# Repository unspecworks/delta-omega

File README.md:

# DELTA OMEGA

A portable ultra-low-profile (ULP) wireless 3×5+2 split keyboard.

## Overview

- Switch support: Cherry MX ULP or Kailh PG1316s
- 34 keys, splayed and staggered with choc spacing
- Wireless
- CNC aluminum case

## Parameters

## Documentation

> [!NOTE]
> This is **not** a typical low-profile (LP) or MX build. While it may look familiar, there are enough differences here that skipping the documentation could cause issues. Please take the time to read all notes and guides before starting.

- [Getting Started](./docs/GETTING_STARTED.md)
- [Bill of Materials](./docs/BOM.md)
- [Build Guides](./docs/BUILD_GUIDES.md)
- [Video](https://youtu.be/UktrqN3MlLI)
- [PCB](./pcb/README.md)
- [Case](./case/README.md)
- [ZMK Keyboard Module](https://github.com/unspecworks/zmk-keyboard-delta-omega)
- [Pre-conf ZMK Config](https://github.com/unspecworks/zmk-delta-omega)
- Keycaps
  - [Delta ULP Keycap](https://github.com/unspecworks/delta-ulp-keycap)

## Photos

- [Gallery](./gallery/README.md)
- [Prototype Gallery](./images/README.md)
  - Diff: Port position, Thumb-cluster layout and only hot-plate way.

## Acknowledgments and Inspirations

- [GEIGEIGEIST/TOTEM](https://github.com/GEIGEIGEIST/TOTEM)
- [mikeholscher/zmk-config-mikecinq](https://github.com/mikeholscher/zmk-config-mikecinq)
- [pashutk/Cherry_MX_ULP](https://github.com/pashutk/Cherry_MX_ULP)
- [zmk-rgbled-widget](https://github.com/caksoylar/zmk-rgbled-widget)
- [infused-kim/kb_ergogen_fp](https://github.com/infused-kim/kb_ergogen_fp)
- [ceoloide/ergogen-footprints](https://github.com/ceoloide/ergogen-footprints)
- [kiswitch/kiswitch](https://github.com/kiswitch/kiswitch)

## Limitations and Disclaimer

This is a hobby-driven project. Some aspects may be incomplete, imperfect, or problematic. Use this project **at your own risk**, and note that no warranties or guarantees are provided.

## License

DELTA OMEGA is licensed under [CERN-OHL-W-2.0](./LICENSE.md).

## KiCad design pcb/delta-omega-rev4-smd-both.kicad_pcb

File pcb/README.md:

# PCB

> [!TIP]
> If this is your first visit, please read the [Getting Started guide](./../docs/GETTING_STARTED.md) first.

---

## PCB List

| File | Description | Note |
|---|---|---|
| `delta-omega-rev4-handsolder-both` | Main Left & Right PCB with mouse-bite connection | MB Not tested. |
| `delta-omega-rev4-handsolder-left` | Main Left PCB | |
| `delta-omega-rev4-handsolder-right` | Main Right PCB | |
| `delta_omega_bottom_cover` | Bottom cover PCB plate | Reversible |
| ... |  |  |
| `delta-omega-rev4-smd-both` | SMD Version | :warning: NOT TESTED |

---

## How to Order

This guide is written based on **[JLCPCB](https://jlcpcb.com)**. While other PCB manufacturers may differ slightly, most ordering steps are very similar.

To place an order, you will need the **Gerber archive**. Simply upload the ZIP file found in [./gerbers/](./gerbers/) to the JLCPCB order page.

> [!NOTE]
> In JLCPCB’s Gerber Viewer, the edge cuts for hand-soldering switch may not appear. This is a known JLCPCB viewer issue and does **not** affect the actual manufacturing.

---

### Recommended Options

| Specification     | Recommended                          | Notes                                                                 |
|-------------------|--------------------------------------|----------------------------------------------------------------------|
| Base Material     | FR-4                                 | Standard PCB substrate material                                      |
| Layers            | 2                                    | Two-layer board                                                      |
| PCB Quantity      | As many as needed                    |                                                                      |
| Product Type      | Industrial / Consumer Electronics    |                                                                      |
| Different Designs | 1                                    | If uploading a combined left & right PCB Gerber, select **2**.[^1]   |
| PCB Thickness     | 0.8 mm or 1.6 mm                     | See [Getting Started](./../docs/GETTING_STARTED.md) for details         |
| PCB Color         | Your preference                      |                                                                      |
| Surface Finish    | Your preference                      |                                                                      |
| Mark on PCB       | Remove Mark                          | Recommended for a cleaner finish                                     |

[^1]: If not selected, JLCPCB will automatically review your order and guide you to the correct option.

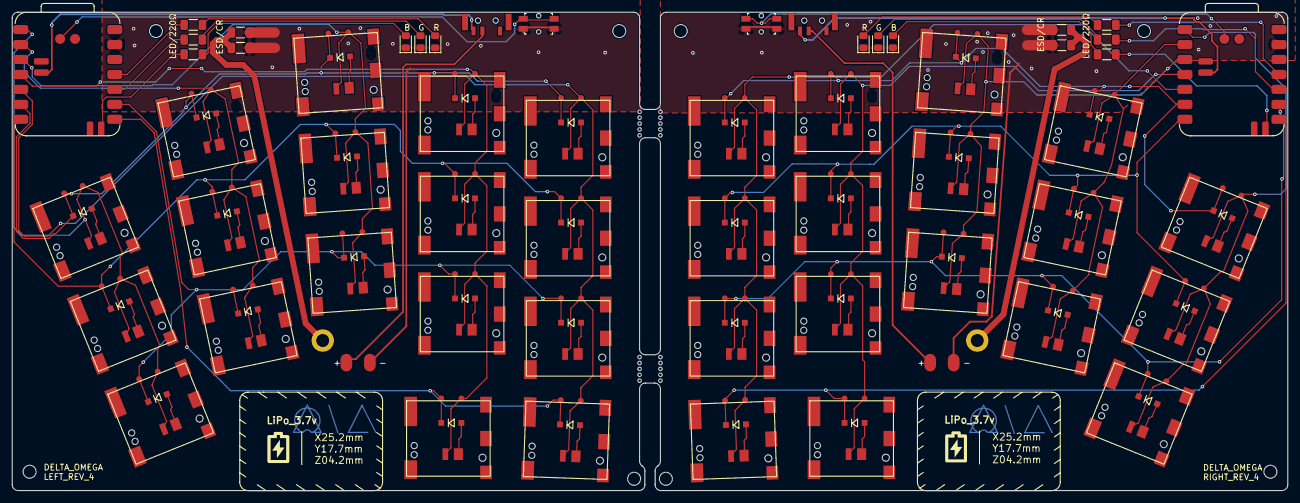
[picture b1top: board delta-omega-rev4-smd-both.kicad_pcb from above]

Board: 2 copper layers, 216.5 x 81.2 mm, 102 parts (0 on the bottom side), 74 nets.

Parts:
C1, C2: C_1206_1NF; C_1206_3216Metric_Pad1.33x1.80mm_HandSolder
D1, D2, D3, D4, D5, D6, D7, D8, D9, D10, D11, D12, D13, D14, D15, D16, D17, D18, D19, D20, D21, D22, D23, D24, D25, D26, D27, D28, D29, D30, D31, D32, D33, D34: SOD123
H1, H2: mounting_hole_plated
L1, L4: LED_0805_R; LED_0805_2012Metric_Pad1.15x1.40mm_HandSolder
L2, L5: LED_0805_G; LED_0805_2012Metric_Pad1.15x1.40mm_HandSolder
L3, L6: LED_0805_B; LED_0805_2012Metric_Pad1.15x1.40mm_HandSolder
MCU1, MCU2: XIAO-nRF52840-SMD; smdXIAO-nRF52840
MH1, MH2, MH3, MH4, MH5, MH6, MH7, MH8: mounting_hole_npth
POWER1: PWR_SW; power_switch
PWR_SW: POWER1; power_switch
R1, R2, R3, R4, R5, R6: R_1206 _220R; R_1206_3216Metric_Pad1.30x1.75mm_HandSolder
R7, R8: R_1206_1MR; C_1206_3216Metric_Pad1.33x1.80mm_HandSolder
RST1, RST2: SW_RST; reset_switch_smd_side
SW1, SW2, SW3, SW4, SW5, SW6, SW7, SW8, SW9, SW10, SW11, SW12, SW13, SW14, SW15, SW16, SW17, SW18, SW19, SW20, SW21, SW22, SW23, SW24, SW25, SW26, SW27, SW28, SW29, SW30, SW31, SW32, SW33, SW34: ULP_SW; GENERIC_ULP_SMD
TH1, TH2: simple_tht_fp

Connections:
L_BATP: MCU2.15, POWER1.3
L_C1: MCU2.1, SW1.1, SW2.1, SW3.1
L_C2: MCU2.2, SW4.1, SW5.1, SW6.1
L_C3: MCU2.3, SW7.1, SW8.1, SW9.1
L_C4: MCU2.4, SW10.1, SW11.1, SW12.1, SW16.1
L_C5: MCU2.5, SW13.1, SW14.1, SW15.1, SW17.1
L_CGND: C2.1, R8.1
L_GND: C2.2, L4.1, L5.1, L6.1, MCU2.13, R8.2, RST1.2, RST1.4, TH1.1
L_LED1: L4.2, R1.2
L_LED2: L5.2, R2.2
L_LED3: L6.2, R3.2
L_LED_R1: MCU2.11, R1.1
L_LED_R2: MCU2.10, R2.1
L_LED_R3: MCU2.17, R3.1
L_R1: D3.4, D6.4, D9.4, D12.4, D15.4, MCU2.6, SW3.4, SW6.4, SW9.4, SW12.4, SW15.4
L_R2: D2.4, D5.4, D8.4, D11.4, D14.4, MCU2.7, SW2.4, SW5.4, SW8.4, SW11.4, SW14.4
L_R3: D1.4, D4.4, D7.4, D10.4, D13.4, MCU2.9, SW1.4, SW4.4, SW7.4, SW10.4, SW13.4
L_R4: D16.4, D17.4, MCU2.8, SW16.4, SW17.4
L_RAW: POWER1.2, TH1.2
L_RST: MCU2.21, RST1.1, RST1.3
R_BATP: MCU1.15, PWR_SW.3
R_C1: MCU1.1, SW18.1, SW19.1, SW20.1
R_C2: MCU1.2, SW21.1, SW22.1, SW23.1
R_C3: MCU1.3, SW24.1, SW25.1, SW26.1
R_C4: MCU1.4, SW27.1, SW28.1, SW29.1, SW33.1
R_C5: MCU1.5, SW30.1, SW31.1, SW32.1, SW34.1
R_CGND: C1.2, R7.2
R_GND: C1.1, L1.1, L2.1, L3.1, MCU1.13, R7.1, RST2.2, RST2.4, TH2.1
R_LED1: L1.2, R4.1
R_LED2: L2.2, R5.1
R_LED3: L3.2, R6.1
R_LED_R1: MCU1.11, R4.2
R_LED_R2: MCU1.10, R5.2
R_LED_R3: MCU1.17, R6.2
R_R1: D20.4, D23.4, D26.4, D29.4, D32.4, MCU1.6, SW20.4, SW23.4, SW26.4, SW29.4, SW32.4
R_R2: D19.4, D22.4, D25.4, D28.4, D31.4, MCU1.7, SW19.4, SW22.4, SW25.4, SW28.4, SW31.4
R_R3: D18.4, D21.4, D24.4, D27.4, D30.4, MCU1.9, SW18.4, SW21.4, SW24.4, SW27.4, SW30.4
R_R4: D33.4, D34.4, MCU1.8, SW33.4, SW34.4
R_RAW: PWR_SW.2, TH2.2
R_RST: MCU1.21, RST2.1, RST2.3
SW1_1: D1.5, SW1.2
SW2_1: D2.5, SW2.2
SW3_1: D3.5, SW3.2
SW4_1: D4.5, SW4.2
SW5_1: D5.5, SW5.2
SW6_1: D6.5, SW6.2
SW7_1: D7.5, SW7.2
SW8_1: D8.5, SW8.2
SW9_1: D9.5, SW9.2
SW10_1: D10.5, SW10.2
SW11_1: D11.5, SW11.2
SW12_1: D12.5, SW12.2
SW13_1: D13.5, SW13.2
SW14_1: D14.5, SW14.2
SW15_1: D15.5, SW15.2
SW16_1: D16.5, SW16.2
SW17_1: D17.5, SW17.2
SW18_1: D18.5, SW18.2
SW19_1: D19.5, SW19.2
SW20_1: D20.5, SW20.2
SW21_1: D21.5, SW21.2
SW22_1: D22.5, SW22.2
SW23_1: D23.5, SW23.2
SW24_1: D24.5, SW24.2
SW25_1: D25.5, SW25.2
SW26_1: D26.5, SW26.2
SW27_1: D27.5, SW27.2
SW28_1: D28.5, SW28.2
SW29_1: D29.5, SW29.2
SW30_1: D30.5, SW30.2
SW31_1: D31.5, SW31.2
SW32_1: D32.5, SW32.2
SW33_1: D33.5, SW33.2
SW34_1: D34.5, SW34.2

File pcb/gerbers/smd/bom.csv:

Designator,Footprint,Quantity,Value,LCSC Part #
"_4, _3, _2, ",Mousebite_5,4,,
"C1, C2",1206,2,C_1206_1NF,C1845
"D1, D10, D11, D12, D13, D14, D15, D16, D17, D18, D19, D2, D20, D21, D22, D23, D24, D25, D26, D27, D28, D29, D3, D30, D31, D32, D33, D34, D4, D5, D6, D7, D8, D9",SOD123,34,SOD123,C917030
"H1, H2",mounting_hole_plated,2,,
"L1, L4",0805,2,LED_0805_R,C19171391
"L2, L5",0805,2,LED_0805_G,C25170728
"L3, L6",0805,2,LED_0805_B,C19273154
"MCU1, MCU2",smdXIAO-nRF52840,2,XIAO-nRF52840-SMD,
"MH1, MH2, MH3, MH4, MH5, MH6, MH7, MH8",mounting_hole_npth,8,,
POWER1,power_switch,1,PWR_SW,C2911519
PWR_SW,power_switch,1,POWER1,C2911519
"R1, R2, R3, R4, R5, R6",1206,6,R_1206 _220R,C17957
"R7, R8",1206,2,R_1206_1MR,C17927
"RST1, RST2",reset_switch_smd_side,2,SW_RST,C79175
"SW1, SW10, SW11, SW12, SW13, SW14, SW15, SW16, SW17, SW18, SW19, SW2, SW20, SW21, SW22, SW23, SW24, SW25, SW26, SW27, SW28, SW29, SW3, SW30, SW31, SW32, SW33, SW34, SW4, SW5, SW6, SW7, SW8, SW9",GENERIC_ULP_SMD,34,ULP_SW,C48887637
"TH1, TH2",simple_tht_fp,2,,

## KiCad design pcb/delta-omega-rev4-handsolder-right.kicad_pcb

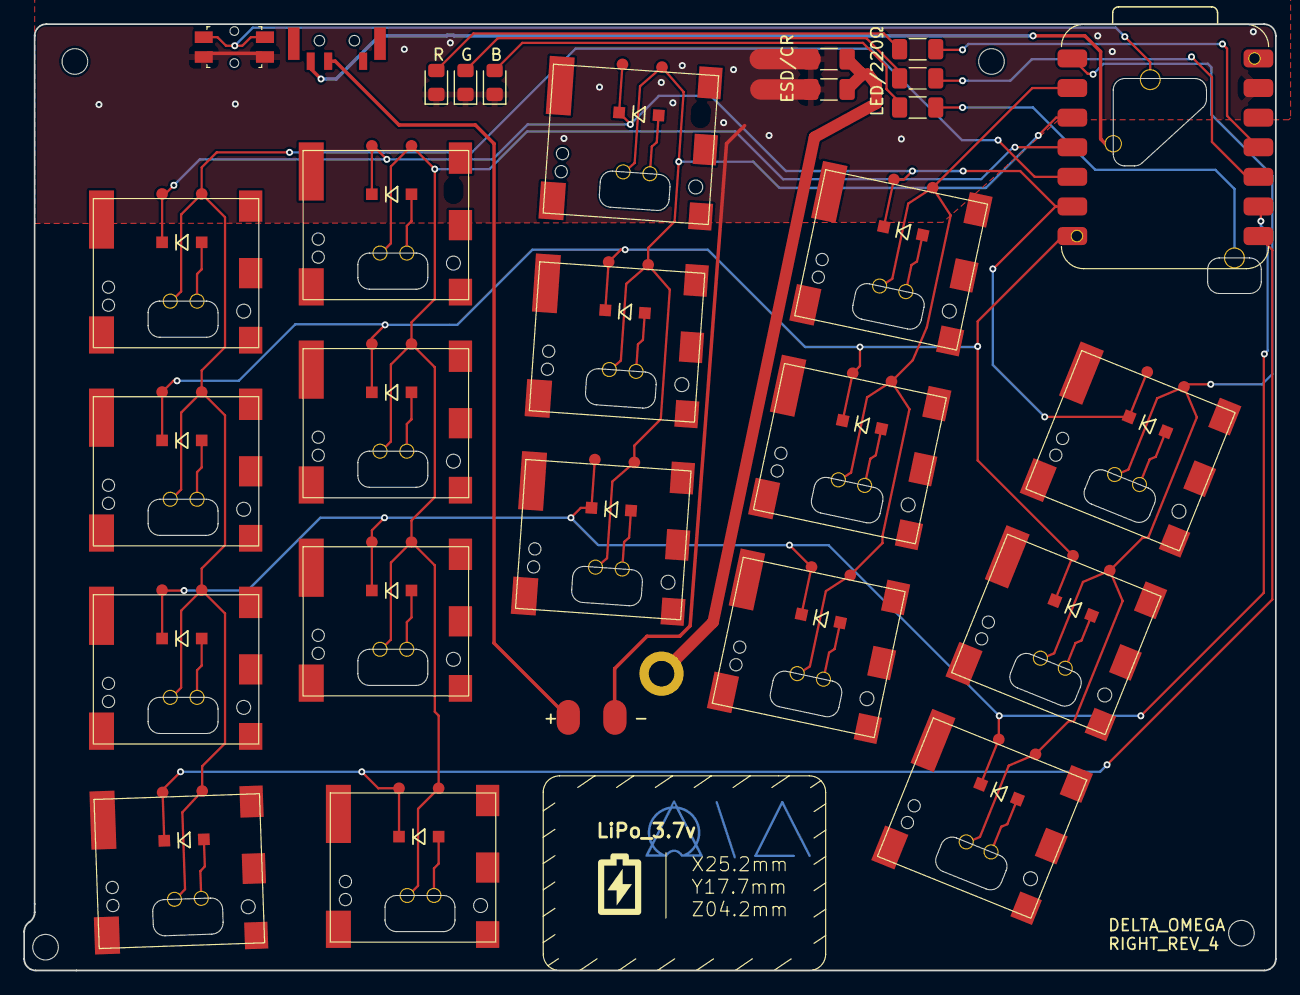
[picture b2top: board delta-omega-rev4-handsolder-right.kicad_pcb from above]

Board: 2 copper layers, 107.4 x 81.2 mm, 33 parts (0 on the bottom side), 35 nets.

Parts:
C1: C_1206_3216Metric_Pad1.33x1.80mm_HandSolder
H2: mounting_hole_plated
L1, L2, L3: LED_0805_2012Metric_Pad1.15x1.40mm_HandSolder
MCU1: XIAO-nRF52840-SMD; XIAO-nRF52840
MH2, MH4, MH6, MH8: mounting_hole_npth
R1, R2, R3: R_1206_3216Metric_Pad1.30x1.75mm_HandSolder
R1#2: C_1206_3216Metric_Pad1.33x1.80mm_HandSolder
RST2: reset_switch_smd_side
SW18, SW19, SW20, SW21, SW22, SW23, SW24, SW25, SW26, SW27, SW28, SW29, SW30, SW31, SW32, SW33, SW34: ULP_SW; GENERIC_ULP_HANDSOLDER
TH2: simple_tht_fp

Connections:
R_C1: MCU1.1, SW18.1, SW19.1, SW20.1
R_C2: MCU1.2, SW21.1, SW22.1, SW23.1
R_C3: MCU1.3, SW24.1, SW25.1, SW26.1
R_C4: MCU1.4, SW27.1, SW28.1, SW29.1, SW33.1
R_C5: MCU1.5, SW30.1, SW31.1, SW32.1, SW34.1
R_CGND: C1.2, R1#2.2
R_GND: C1.1, L1.1, L2.1, L3.1, MCU1.13, R1#2.1, RST2.2, RST2.4, TH2.1
R_LED1: L1.2, R1.1
R_LED2: L2.2, R2.1
R_LED3: L3.2, R3.1
R_LED_R1: MCU1.11, R1.2
R_LED_R2: MCU1.10, R2.2
R_LED_R3: MCU1.17, R3.2
R_R1: MCU1.6, SW20.4, SW23.4, SW26.4, SW29.4, SW32.4
R_R2: MCU1.7, SW19.4, SW22.4, SW25.4, SW28.4, SW31.4
R_R3: MCU1.9, SW18.4, SW21.4, SW24.4, SW27.4, SW30.4
R_R4: MCU1.8, SW33.4, SW34.4
R_RST: MCU1.21, RST2.1, RST2.3
SW18_1: SW18.2, SW18.5
SW19_1: SW19.2, SW19.5
SW20_1: SW20.2, SW20.5
SW21_1: SW21.2, SW21.5
SW22_1: SW22.2, SW22.5
SW23_1: SW23.2, SW23.5
SW24_1: SW24.2, SW24.5
SW25_1: SW25.2, SW25.5
SW26_1: SW26.2, SW26.5
SW27_1: SW27.2, SW27.5
SW28_1: SW28.2, SW28.5
SW29_1: SW29.2, SW29.5
SW30_1: SW30.2, SW30.5
SW31_1: SW31.2, SW31.5
SW32_1: SW32.2, SW32.5
SW33_1: SW33.2, SW33.5
SW34_1: SW34.2, SW34.5

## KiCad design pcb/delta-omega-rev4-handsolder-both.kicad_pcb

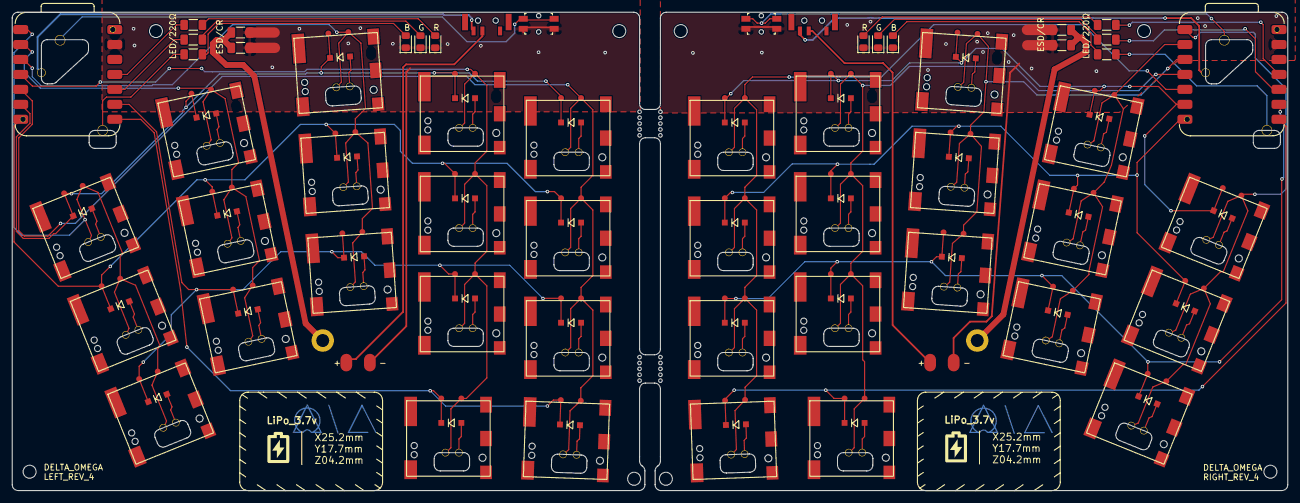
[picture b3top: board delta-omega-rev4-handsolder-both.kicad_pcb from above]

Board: 2 copper layers, 216.5 x 81.2 mm, 66 parts (0 on the bottom side), 70 nets.

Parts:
C1, C1#2: C_1206_3216Metric_Pad1.33x1.80mm_HandSolder
H1, H2: mounting_hole_plated
L1, L1#2, L2, L2#2, L3, L3#2: LED_0805_2012Metric_Pad1.15x1.40mm_HandSolder
MCU1, MCU2: XIAO-nRF52840-SMD; XIAO-nRF52840
MH1, MH2, MH3, MH4, MH5, MH6, MH7, MH8: mounting_hole_npth
R1, R1#3, R2, R2#2, R3, R3#2: R_1206_3216Metric_Pad1.30x1.75mm_HandSolder
R1#2, R1#4: C_1206_3216Metric_Pad1.33x1.80mm_HandSolder
RST1, RST2: reset_switch_smd_side
SW1, SW2, SW3, SW4, SW5, SW6, SW7, SW8, SW9, SW10, SW11, SW12, SW13, SW14, SW15, SW16, SW17, SW18, SW19, SW20, SW21, SW22, SW23, SW24, SW25, SW26, SW27, SW28, SW29, SW30, SW31, SW32, SW33, SW34: ULP_SW; GENERIC_ULP_HANDSOLDER
TH1, TH2: simple_tht_fp

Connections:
L_C1: MCU2.1, SW1.1, SW2.1, SW3.1
L_C2: MCU2.2, SW4.1, SW5.1, SW6.1
L_C3: MCU2.3, SW7.1, SW8.1, SW9.1
L_C4: MCU2.4, SW10.1, SW11.1, SW12.1, SW16.1
L_C5: MCU2.5, SW13.1, SW14.1, SW15.1, SW17.1
L_CGND: C1#2.1, R1#2.1
L_GND: C1#2.2, L1.1, L2#2.1, L3#2.1, MCU2.13, R1#2.2, RST1.2, RST1.4, TH1.1
L_LED1: L1.2, R1#3.2
L_LED2: L2#2.2, R2#2.2
L_LED3: L3#2.2, R3#2.2
L_LED_R1: MCU2.11, R1#3.1
L_LED_R2: MCU2.10, R2#2.1
L_LED_R3: MCU2.17, R3#2.1
L_R1: MCU2.6, SW3.4, SW6.4, SW9.4, SW12.4, SW15.4
L_R2: MCU2.7, SW2.4, SW5.4, SW8.4, SW11.4, SW14.4
L_R3: MCU2.9, SW1.4, SW4.4, SW7.4, SW10.4, SW13.4
L_R4: MCU2.8, SW16.4, SW17.4
L_RST: MCU2.21, RST1.1, RST1.3
R_C1: MCU1.1, SW18.1, SW19.1, SW20.1
R_C2: MCU1.2, SW21.1, SW22.1, SW23.1
R_C3: MCU1.3, SW24.1, SW25.1, SW26.1
R_C4: MCU1.4, SW27.1, SW28.1, SW29.1, SW33.1
R_C5: MCU1.5, SW30.1, SW31.1, SW32.1, SW34.1
R_CGND: C1.2, R1#4.2
R_GND: C1.1, L1#2.1, L2.1, L3.1, MCU1.13, R1#4.1, RST2.2, RST2.4, TH2.1
R_LED1: L1#2.2, R1.1
R_LED2: L2.2, R2.1
R_LED3: L3.2, R3.1
R_LED_R1: MCU1.11, R1.2
R_LED_R2: MCU1.10, R2.2
R_LED_R3: MCU1.17, R3.2
R_R1: MCU1.6, SW20.4, SW23.4, SW26.4, SW29.4, SW32.4
R_R2: MCU1.7, SW19.4, SW22.4, SW25.4, SW28.4, SW31.4
R_R3: MCU1.9, SW18.4, SW21.4, SW24.4, SW27.4, SW30.4
R_R4: MCU1.8, SW33.4, SW34.4
R_RST: MCU1.21, RST2.1, RST2.3
SW1_1: SW1.2, SW1.5
SW2_1: SW2.2, SW2.5
SW3_1: SW3.2, SW3.5
SW4_1: SW4.2, SW4.5
SW5_1: SW5.2, SW5.5
SW6_1: SW6.2, SW6.5
SW7_1: SW7.2, SW7.5
SW8_1: SW8.2, SW8.5
SW9_1: SW9.2, SW9.5
SW10_1: SW10.2, SW10.5
SW11_1: SW11.2, SW11.5
SW12_1: SW12.2, SW12.5
SW13_1: SW13.2, SW13.5
SW14_1: SW14.2, SW14.5
SW15_1: SW15.2, SW15.5
SW16_1: SW16.2, SW16.5
SW17_1: SW17.2, SW17.5
SW18_1: SW18.2, SW18.5
SW19_1: SW19.2, SW19.5
SW20_1: SW20.2, SW20.5
SW21_1: SW21.2, SW21.5
SW22_1: SW22.2, SW22.5
SW23_1: SW23.2, SW23.5
SW24_1: SW24.2, SW24.5
SW25_1: SW25.2, SW25.5
SW26_1: SW26.2, SW26.5
SW27_1: SW27.2, SW27.5
SW28_1: SW28.2, SW28.5
SW29_1: SW29.2, SW29.5
SW30_1: SW30.2, SW30.5
SW31_1: SW31.2, SW31.5
SW32_1: SW32.2, SW32.5
SW33_1: SW33.2, SW33.5
SW34_1: SW34.2, SW34.5

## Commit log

2025-08-15 prototype v1 done.
2025-08-15 Add more todos
    many good ppl ask or criticism for this. really appreciated. i love this powerful community.
2025-08-17 Add some improvements for prototype
2025-08-19 Some updates
2025-08-31 documentation.
2025-09-08 Added firmware link Added Led indicator issue Added Some quick links
2025-09-13 Removed LED Indicator. and clean up docs.
    - NeoPixel still drains so much power. and not a handy feature.
2025-09-13 Updated the incorrect image content.
2025-09-21 update documents
2025-10-12 Release ready
2025-10-12 Updated firmware links
2025-10-12 Added more photos
2025-10-12 Added Layout image
2025-10-12 Add prototype gallery
2025-10-12 Add more photos
2025-10-23 Update buying options with locations
2025-10-23 Fix link to Getting Started documentation
    Updated the link to the Getting Started documentation.
2025-10-28 Fix PCB file name in pcb/README.md
2025-11-02 Added more images.
2025-11-03 Add Video link to README
2025-11-04 doc: update getting started with some tips
    Clarified details about keycap sourcing and actuation force considerations. and more.
2025-12-05 pcb: add smd pcb and gerbers
